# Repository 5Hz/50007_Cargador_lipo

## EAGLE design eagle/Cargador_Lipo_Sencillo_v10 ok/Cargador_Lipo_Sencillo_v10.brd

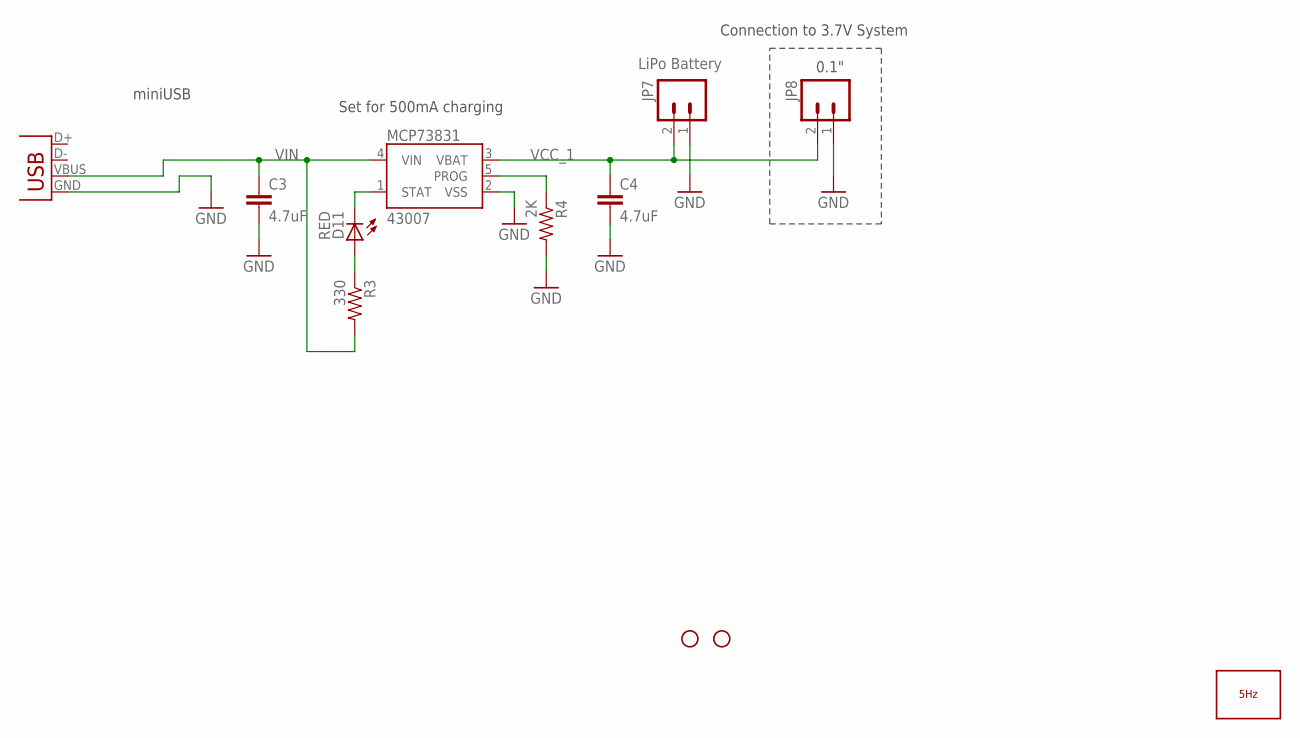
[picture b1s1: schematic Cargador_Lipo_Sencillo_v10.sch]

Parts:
C3, C4: 4.7uF; 0603-CAP
D11: RED; LED-0603
JP1, JP2: STAND-OFF
JP7: LiPo Battery; JST-2-SMD
JP8: M02POLAR; MOLEX-1X2
LOGO1: LOGO_5HZ_H_10MM; 5HZ_LOGO_H_10MM
MCP73831: 43007; SOT23-5
R3: 330; 0603-RES
R4: 2K; 0603-RES
X1: USBSMD; USB-MINIB

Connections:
GND: C3.2, C4.2, JP7.1, JP8.1, MCP73831.2 (VSS), R4.2, X1.GND
unnamed: D11.A, R3.1
PROG: MCP73831.5 (PROG), R4.1
STAT: D11.C, MCP73831.1 (STAT)
VCC_1: C4.1, JP7.2, JP8.2, MCP73831.3 (VBAT)
VIN: C3.1, MCP73831.4 (VIN), R3.2, X1.VBUS

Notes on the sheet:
Set for 500mA charging
Connection to 3.7V System
0.1"
miniUSB

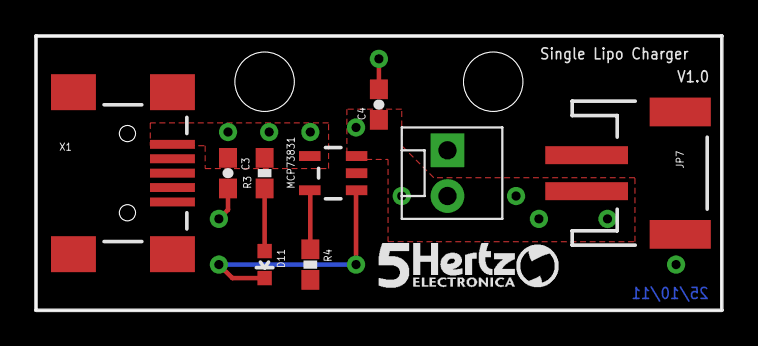
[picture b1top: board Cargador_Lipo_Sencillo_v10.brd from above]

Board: 2 copper layers, 38.1 x 15.2 mm, 12 parts (0 on the bottom side), 6 nets.

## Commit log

2014-01-09 creación
